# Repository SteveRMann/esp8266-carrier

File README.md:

# esp8266-carrier
A universal carrier board for the ESP8266-01

The board design allows for a buck voltage converter to allow up to 24VDC Vin, and also accepts a three-pin 3V3 regulator (same pinout).

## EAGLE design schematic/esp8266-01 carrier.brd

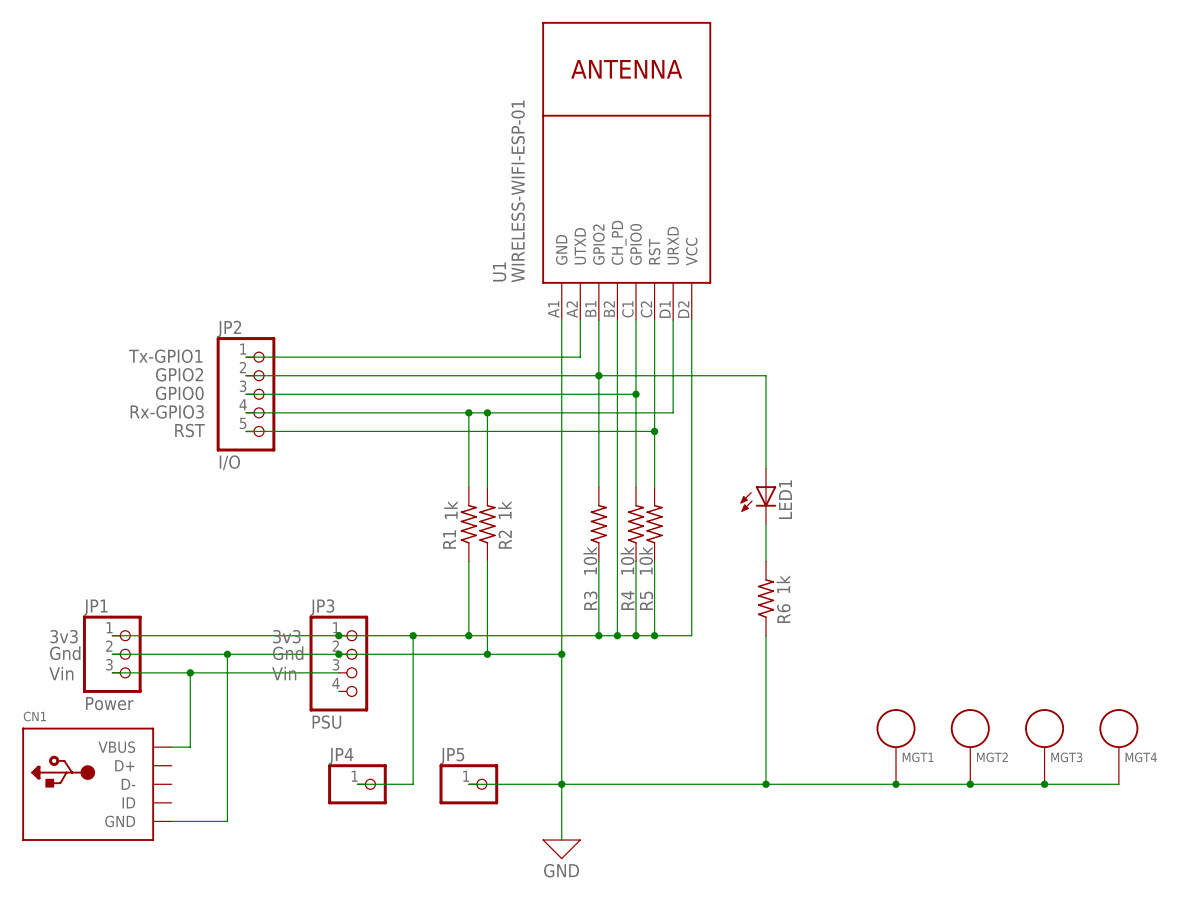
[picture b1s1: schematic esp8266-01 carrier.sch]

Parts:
CN1: USBTHM; USB-MINIB-THM
JP1: Power; 1X03
JP2: I/O; 1X05
JP3: PSU; 1X04
JP4, JP5: PINHD-1X1; 1X01
LED1: LED5MM
MGT1, MGT2, MGT3, MGT4: BEAGLEBONEBLACK_MOUNTING_HOLE
R1, R2, R6: 1k; 0207/10
R3, R4, R5: 10k; 0207/10
U1: WIRELESS-WIFI-ESP-01

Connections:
3V3: JP1.1, JP3.1, JP4.1, R1.1, R3.1, R4.1, R5.1, U1.B2 (CH_PD), U1.D2 (VCC)
GND: CN1.GND, JP1.2, JP3.2, JP5.1, MGT1.P$1, MGT2.P$1, MGT3.P$1, MGT4.P$1, R2.1, R6.1, U1.A1 (GND)
unnamed: LED1.K (C), R6.2
unnamed: JP2.2, LED1.A, R3.2, U1.B1 (GPIO2)
unnamed: CN1.VBUS, JP1.3, JP3.3
unnamed: JP2.3, R4.2, U1.C1 (GPIO0)
unnamed: JP2.5, R5.2, U1.C2 (RST)
unnamed: JP2.4, R1.2, R2.2, U1.D1 (URXD)
TX-GPIO1: JP2.1, U1.A2 (UTXD)

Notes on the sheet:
Gnd
Vin
3v3
Tx-GPIO1
GPIO2
GPIO0
Rx-GPIO3
RST

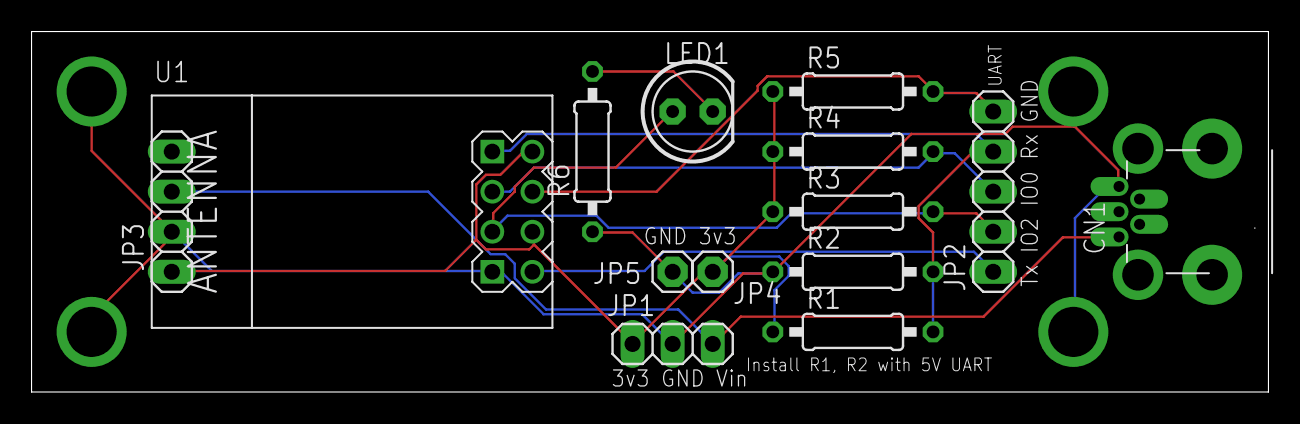
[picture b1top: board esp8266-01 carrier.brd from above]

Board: 2 copper layers, 78.4 x 22.8 mm, 18 parts (0 on the bottom side), 9 nets.

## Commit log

2022-03-18 Create esp8266-01 carrier
2022-03-18 Create tmp
2022-03-18 Add files via upload
    Gerber files for pcb.
2022-04-24 Added USB, gitignore

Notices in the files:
parts and their libraries:
diy-modules: Released under the Creative Commons Attribution 4.0 International License: http://creativecommons.org/licenses/by/4.0
